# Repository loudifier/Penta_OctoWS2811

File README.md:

# Penta_OctoWS2811
Adapter board for driving 40 channels of WS2811-style addressable LED strips with a Teensy 4.1 microcontroller

This is a work in progress. A prototype board has been assembled, but I am waiting on parts to test Ethernet, and I am working on a sketch for testing that works better than the teensyduino examples for thousands of LEDs. Committing what I have so far.

[photo of board and LEDs]

The **Penta**_OctoWS2811 is effectively five of the [PJRC OctoWS2811 adapter](https://www.pjrc.com/store/octo28_adaptor.html) squished into a single board for an easy way to take full advantage of the Teensy 4.1's ability to use any set of GPIO pins with the OctoWS2811 library. Penta_OctoWS2811 also adds an Ethernet connector for use with ArtNet or other networked light controller, and a voltage regulator so the board and Teensy can be powered from the LED power supply without USB.

[image of schematic]

## Features

The Penta_OctoWS2811 board has 10 RJ45 ports, for a total of 40 output channels driven from 5V buffers through 100Ω termination resistors. Teensy 4.0 can also be used with this board, supporting up to 24 output channels.

## Usage

The instructions and guidelines on the PJRC website and Teensyduino example scketches for using a Teensy and OctoWS2811 to drive addressible LED strips over CAT6 wires apply equally to the PJRC OctoWS2811 adapter and the Penta_OctoWS2811 board, except for a few key features noted below.

### Output Pins

Teensy 4.1 digital output pins are connected to the following RJ45 ports:  
 Port - GPIO pins  
  J2 - 1, 2, 3, 4  
  J3 - 5, 6, 7, 8  
  J4 - 25, 26, 27, 28  
  J5 - 29, 30, 31, 32  
  J6 - 23, 22, 21, 20  
  J7 - 17, 16, 15, 14  
  J8 - 40, 39, 38, 37  
  J9 - 36, 35, 34, 33  
  J10 - 13, 18, 19, 9  
  J11 - 11, 12, 41, 24

Teensy 4.0 is compatible with the board, and will be connected to J2, J3, J6, J7, J10, and J11. In order to get a full 24 channels of output with Teensy 4.0, GPIO 0 can be used instead of GPIO 41 and GPIO 12 can be used instead of GPIO 24 by shorting jumper pads on the bottom of the board.

A frame sync output is provided, if you somehow need even more output channels and need to maintain accurate timing between multiple boards. The connector can also be useful for connecting to a single 3.3V-compatible LED strip. If you need to use GPIO 12 for SPI communication, you can cut and jump the appropriate pads on the bottom of the board to use GPIO 0 instead.

### Power

Just like the PJRC OctoWS2811 adapter, the Penta_OctoWS2811 board can be powered from your LED power supply. The Penta_OctoWS2811 board adds a voltage regulator for compatibility with newer 12V LED strips. If you are using 5V LEDs, the voltage regulator should be bypassed using the jumper pads on top of the board.

**The Teensy VUSB jumper must be cut if you plan to power the board from the LED power supply.** If you cut the VUSB jumper you can add a single header pin connection fom the Teensy VUSB pad to a corresponding pad on the board, which will allow the Teensy and board to be powered from the LED power supply or USB via a diode.

### Ethernet

## Board Design, Pre-assembled Boards

## Testing

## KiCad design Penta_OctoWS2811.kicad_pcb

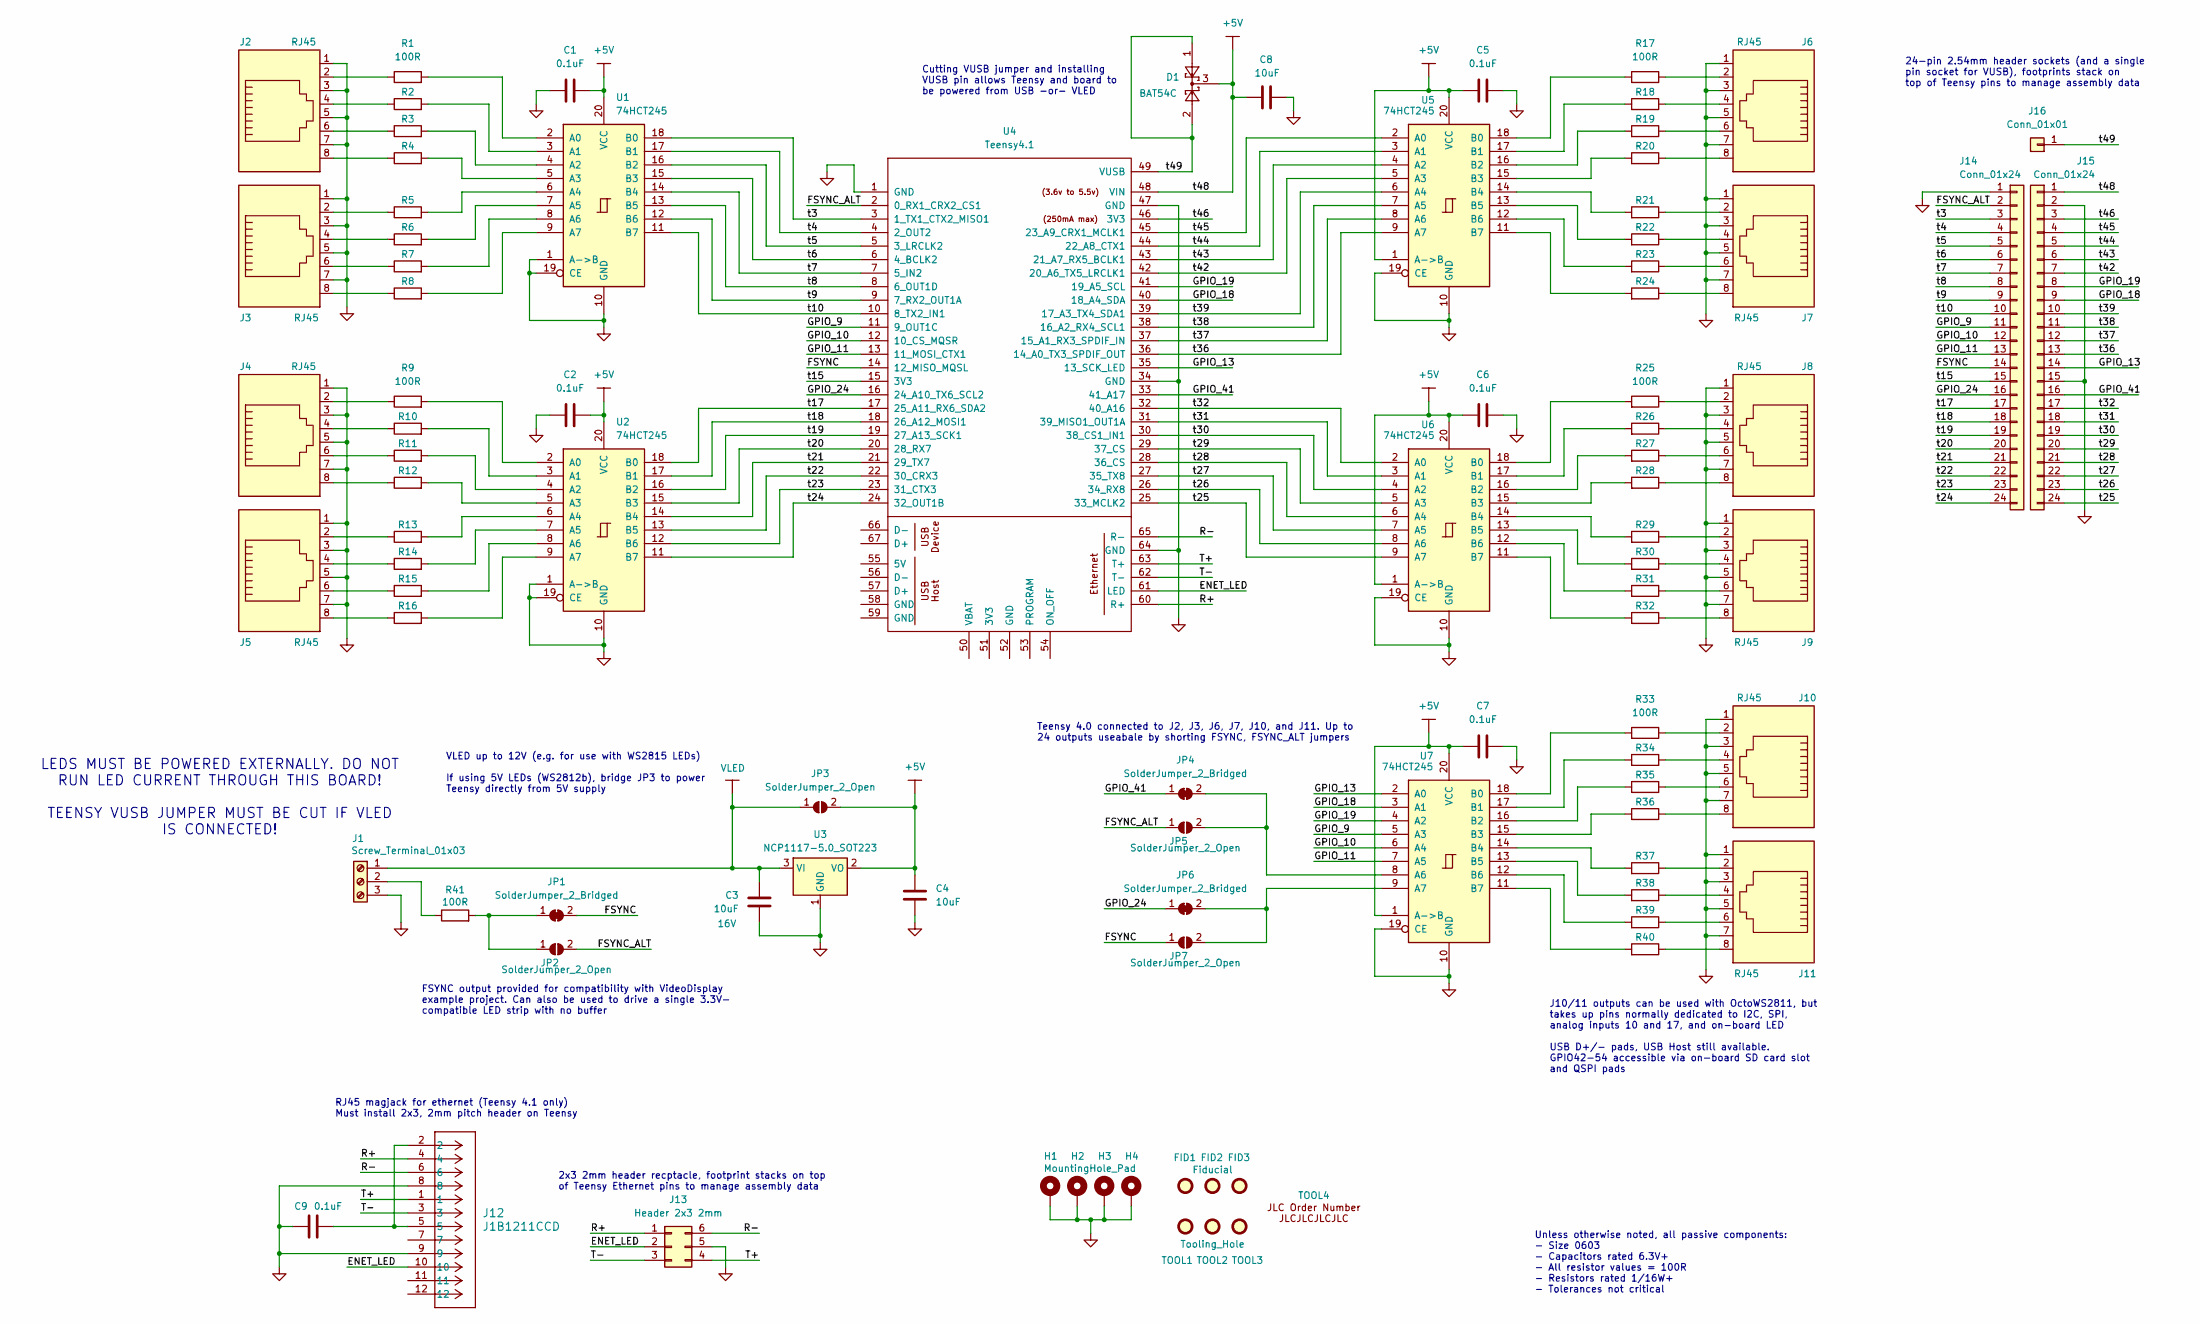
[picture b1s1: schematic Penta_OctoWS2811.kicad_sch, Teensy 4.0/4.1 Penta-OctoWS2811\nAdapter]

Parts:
C1, C2, C5, C6, C7, C9: 0.1uF; C_0603_1608Metric_Pad1.08x0.95mm_HandSolder; Manufacturer Part Number CC0603KRX7R9BB104
C3: 10uF; C_0603_1608Metric_Pad1.08x0.95mm_HandSolder; Voltage 16V; Manufacturer Part Number CL10A106MA8NRNC
C4, C8: 10uF; C_0603_1608Metric_Pad1.08x0.95mm_HandSolder; Manufacturer Part Number CL10A106MA8NRNC
D1: BAT54C; SOT-23; Manufacturer Part Number BAT54C,215
FID1, FID2, FID3: Fiducial; Fiducial_0.5mm_Mask1mm
H1, H2, H3, H4: MountingHole_Pad; MountingHole_5.3mm_M5_Pad
J1: Screw_Terminal_01x03; TerminalBlock_bornier-3_P5.08mm; Manufacturer Part Number DB127V-5.08-3P-GN-S
J2, J3, J4, J5, J6, J7, J8, J9, J10, J11: RJ45; HCTL HC-RJ45-5622-1-6; Manufacturer Part Number HC-RJ45-5622-1-6
J12: J1B1211CCD; CONN12_J1B1211CCD_WIZ; Manufacturer Part Number J1B1211CCD
J13: Header 2x3 2mm; PinSocket_2x03_P2.00mm_Vertical; Manufacturer Part Number ZX-PM2.0-2-3PY
J14, J15: Conn_01x24; PinSocket_1x24_P2.54mm_Vertical; Manufacturer Part Number X6511FV-24-C85D32
J16: Conn_01x01; PinSocket_1x01_P2.54mm_Vertical
JP1, JP4, JP6: SolderJumper_2_Bridged; SolderJumper-2_P1.3mm_Bridged_RoundedPad1.0x1.5mm
JP2, JP3, JP5, JP7: SolderJumper_2_Open; SolderJumper-2_P1.3mm_Open_RoundedPad1.0x1.5mm
R1, R2, R3, R4, R5, R6, R7, R8, R9, R10, R11, R12, R13, R14, R15, R16, R17, R18, R19, R20, R21, R22, R23, R24, R25, R26, R27, R28, R29, R30, R31, R32, R33, R34, R35, R36, R37, R38, R39, R40, R41: 100R; R_0603_1608Metric_Pad0.98x0.95mm_HandSolder; Manufacturer Part Number 0603WAF1000T5E
TOOL1, TOOL2, TOOL3: Tooling_Hole; Tooling Hole
TOOL4: Order Number
U1, U2, U5, U6, U7: 74HCT245; SOIC-20W_7.5x12.8mm_P1.27mm; Manufacturer Part Number 74HCT245D,653
U3: NCP1117-5.0_SOT223; SOT-223-3_TabPin2; Manufacturer Part Number NCP1117LPST50T3G
U4: Teensy4.1; Teensy41

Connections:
+5V: C1.2, C2.2, C4.2, C5.2, C6.2, C7.2, C8.2, D1.3, J15.1, JP3.2 (B), U1.20 (VCC), U2.20 (VCC), U3.2 (VO), U4.48 (VIN), U5.1 (A->B), U5.20 (VCC), U6.1 (A->B), U6.20 (VCC), U7.1 (A->B), U7.20 (VCC)
/ENET_LED: J12.10, J13.2, U4.61 (LED)
/FSYNC: J14.14, JP1.2 (B), JP7.1 (A), U4.14 (12_MISO_MQSL)
/FSYNC_ALT: J14.2, JP2.2 (B), JP5.1 (A), U4.2 (0_RX1_CRX2_CS1)
/GPIO_9: J14.11, U4.11 (9_OUT1C), U7.5 (A3)
/GPIO_10: J14.12, U4.12 (10_CS_MQSR), U7.6 (A4)
/GPIO_11: J14.13, U4.13 (11_MOSI_CTX1), U7.7 (A5)
/GPIO_13: J15.14, U4.35 (13_SCK_LED), U7.2 (A0)
/GPIO_18: J15.9, U4.40 (18_A4_SDA), U7.3 (A1)
/GPIO_19: J15.8, U4.41 (19_A5_SCL), U7.4 (A2)
/GPIO_24: J14.16, JP6.1 (A), U4.16 (24_A10_TX6_SCL2)
/GPIO_41: J15.16, JP4.1 (A), U4.33 (41_A17)
/R+: J12.4, J13.1, U4.60 (R+)
/R-: J12.6, J13.6, U4.65 (R-)
/T+: J12.1, J13.4, U4.63 (T+)
/T-: J12.3, J13.3, U4.62 (T-)
/t3: J14.3, U1.18 (B0), U4.3 (1_TX1_CTX2_MISO1)
/t4: J14.4, U1.17 (B1), U4.4 (2_OUT2)
/t5: J14.5, U1.16 (B2), U4.5 (3_LRCLK2)
/t6: J14.6, U1.15 (B3), U4.6 (4_BCLK2)
/t7: J14.7, U1.14 (B4), U4.7 (5_IN2)
/t8: J14.8, U1.13 (B5), U4.8 (6_OUT1D)
/t9: J14.9, U1.12 (B6), U4.9 (7_RX2_OUT1A)
/t10: J14.10, U1.11 (B7), U4.10 (8_TX2_IN1)
/t15: J14.15, U4.15 (3V3)
/t17: J14.17, U2.18 (B0), U4.17 (25_A11_RX6_SDA2)
/t18: J14.18, U2.17 (B1), U4.18 (26_A12_MOSI1)
/t19: J14.19, U2.16 (B2), U4.19 (27_A13_SCK1)
/t20: J14.20, U2.15 (B3), U4.20 (28_RX7)
/t21: J14.21, U2.14 (B4), U4.21 (29_TX7)
/t22: J14.22, U2.13 (B5), U4.22 (30_CRX3)
/t23: J14.23, U2.12 (B6), U4.23 (31_CTX3)
/t24: J14.24, U2.11 (B7), U4.24 (32_OUT1B)
/t25: J15.24, U4.25 (33_MCLK2), U6.9 (A7)
/t26: J15.23, U4.26 (34_RX8), U6.8 (A6)
/t27: J15.22, U4.27 (35_TX8), U6.7 (A5)
/t28: J15.21, U4.28 (36_CS), U6.6 (A4)
/t29: J15.20, U4.29 (37_CS), U6.5 (A3)
/t30: J15.19, U4.30 (38_CS1_IN1), U6.4 (A2)
/t31: J15.18, U4.31 (39_MISO1_OUT1A), U6.3 (A1)
/t32: J15.17, U4.32 (40_A16), U6.2 (A0)
/t36: J15.13, U4.36 (14_A0_TX3_SPDIF_OUT), U5.9 (A7)
/t37: J15.12, U4.37 (15_A1_RX3_SPDIF_IN), U5.8 (A6)
/t38: J15.11, U4.38 (16_A2_RX4_SCL1), U5.7 (A5)
/t39: J15.10, U4.39 (17_A3_TX4_SDA1), U5.6 (A4)
/t42: J15.7, U4.42 (20_A6_TX5_LRCLK1), U5.5 (A3)
/t43: J15.6, U4.43 (21_A7_RX5_BCLK1), U5.4 (A2)
/t44: J15.5, U4.44 (22_A8_CTX1), U5.3 (A1)
/t45: J15.4, U4.45 (23_A9_CRX1_MCLK1), U5.2 (A0)
/t46: J15.3, U4.46 (3V3)
/t49: D1.1, D1.2, J16.1, U4.49 (VUSB)
GND: C1.1, C2.1, C3.1, C4.1, C5.1, C6.1, C7.1, C8.1, C9.1, H1.1, H2.1, H3.1, H4.1, J1.3, J2.1, J2.3, J2.5, J2.7, J3.1, J3.3, J3.5, J3.7, J4.1, J4.3, J4.5, J4.7, J5.1, J5.3, J5.5, J5.7, J6.1, J6.3, J6.5, J6.7, J7.1, J7.3, J7.5, J7.7, J8.1, J8.3, J8.5, J8.7, J9.1, J9.3, J9.5, J9.7, J10.1, J10.3, J10.5, J10.7, J11.1, J11.3, J11.5, J11.7, J12.8, J12.9, J13.5, J14.1, J15.2, J15.15, U1.1 (A->B), U1.10 (GND), U1.19 (CE), U2.1 (A->B), U2.10 (GND), U2.19 (CE), U3.1 (GND), U4.1 (GND), U4.34 (GND), U4.47 (GND), U4.64 (GND), U5.10 (GND), U5.19 (CE), U6.10 (GND), U6.19 (CE), U7.10 (GND), U7.19 (CE)
unnamed: C9.2, J12.2, J12.5
unnamed: J1.2, R41.1
unnamed: J2.2, R1.1
unnamed: J2.4, R2.1
unnamed: J2.6, R3.1
unnamed: J2.8, R4.1
unnamed: J3.2, R5.1
unnamed: J3.4, R6.1
unnamed: J3.6, R7.1
unnamed: J3.8, R8.1
unnamed: J4.2, R9.1
unnamed: J4.4, R10.1
unnamed: J4.6, R11.1
unnamed: J4.8, R12.1
unnamed: J5.2, R13.1
unnamed: J5.4, R14.1
unnamed: J5.6, R15.1
unnamed: J5.8, R16.1
unnamed: J6.2, R17.1
unnamed: J6.4, R18.1
unnamed: J6.6, R19.1
unnamed: J6.8, R20.1
unnamed: J7.2, R21.1
unnamed: J7.4, R22.1
unnamed: J7.6, R23.1
unnamed: J7.8, R24.1
unnamed: J8.2, R25.1
unnamed: J8.4, R26.1
unnamed: J8.6, R27.1
unnamed: J8.8, R28.1
unnamed: J9.2, R29.1
unnamed: J9.4, R30.1
unnamed: J9.6, R31.1
unnamed: J9.8, R32.1
unnamed: J10.2, R33.1
unnamed: J10.4, R34.1
unnamed: J10.6, R35.1
unnamed: J10.8, R36.1
unnamed: J11.2, R37.1
unnamed: J11.4, R38.1
unnamed: J11.6, R39.1
unnamed: J11.8, R40.1
unnamed: JP1.1 (A), JP2.1 (A), R41.2
unnamed: JP4.2 (B), JP5.2 (B), U7.8 (A6)
unnamed: JP6.2 (B), JP7.2 (B), U7.9 (A7)
unnamed: R1.2, U1.2 (A0)
unnamed: R2.2, U1.3 (A1)
unnamed: R3.2, U1.4 (A2)
unnamed: R4.2, U1.5 (A3)
unnamed: R5.2, U1.6 (A4)
unnamed: R6.2, U1.7 (A5)
unnamed: R7.2, U1.8 (A6)
unnamed: R8.2, U1.9 (A7)
unnamed: R9.2, U2.2 (A0)
unnamed: R10.2, U2.3 (A1)
unnamed: R11.2, U2.4 (A2)
unnamed: R12.2, U2.5 (A3)
unnamed: R13.2, U2.6 (A4)
unnamed: R14.2, U2.7 (A5)
unnamed: R15.2, U2.8 (A6)
unnamed: R16.2, U2.9 (A7)
unnamed: R17.2, U5.18 (B0)
unnamed: R18.2, U5.17 (B1)
unnamed: R19.2, U5.16 (B2)
unnamed: R20.2, U5.15 (B3)
unnamed: R21.2, U5.14 (B4)
unnamed: R22.2, U5.13 (B5)
unnamed: R23.2, U5.12 (B6)
unnamed: R24.2, U5.11 (B7)
unnamed: R25.2, U6.18 (B0)
unnamed: R26.2, U6.17 (B1)
unnamed: R27.2, U6.16 (B2)
unnamed: R28.2, U6.15 (B3)
unnamed: R29.2, U6.14 (B4)
unnamed: R30.2, U6.13 (B5)
unnamed: R31.2, U6.12 (B6)
unnamed: R32.2, U6.11 (B7)
unnamed: R33.2, U7.18 (B0)
unnamed: R34.2, U7.17 (B1)
unnamed: R35.2, U7.16 (B2)
unnamed: R36.2, U7.15 (B3)
unnamed: R37.2, U7.14 (B4)
unnamed: R38.2, U7.13 (B5)
unnamed: R39.2, U7.12 (B6)
unnamed: R40.2, U7.11 (B7)
VLED: C3.2, J1.1, JP3.1 (A), U3.3 (VI)

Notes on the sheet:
Cutting VUSB jumper and installing VUSB pin allows Teensy and board to be powered from USB -or- VLED
2x3 2mm header recptacle, footprint stacks on top of Teensy Ethernet pins to manage assembly data
LEDS MUST BE POWERED EXTERNALLY. DO NOT RUN LED CURRENT THROUGH THIS BOARD! TEENSY VUSB JUMPER MUST BE CUT IF VLED IS CONNECTED!
24-pin 2.54mm header sockets (and a single pin socket for VUSB), footprints stack on top of Teensy pins to manage assembly data
Unless otherwise noted, all passive components: - Size 0603 - Capacitors rated 6.3V+ - All resistor values = 100R - Resistors rated 1/16W+ - Tolerances not critical
FSYNC output provided for compatibility with VideoDisplay example project. Can also be used to drive a single 3.3V- compatible LED strip with no buffer
J10/11 outputs can be used with OctoWS2811, but takes up pins normally dedicated to I2C, SPI, analog inputs 10 and 17, and on-board LED USB D+/- pads, USB Host still available. GPIO42-54 accessible via on-board SD card slot and QSPI pads
RJ45 magjack for ethernet (Teensy 4.1 only) Must install 2x3, 2mm pitch header on Teensy
Teensy 4.0 connected to J2, J3, J6, J7, J10, and J11. Up to 24 outputs useabale by shorting FSYNC, FSYNC_ALT jumpers
VLED up to 12V (e.g. for use with WS2815 LEDs) If using 5V LEDs (WS2812b), bridge JP3 to power Teensy directly from 5V supply

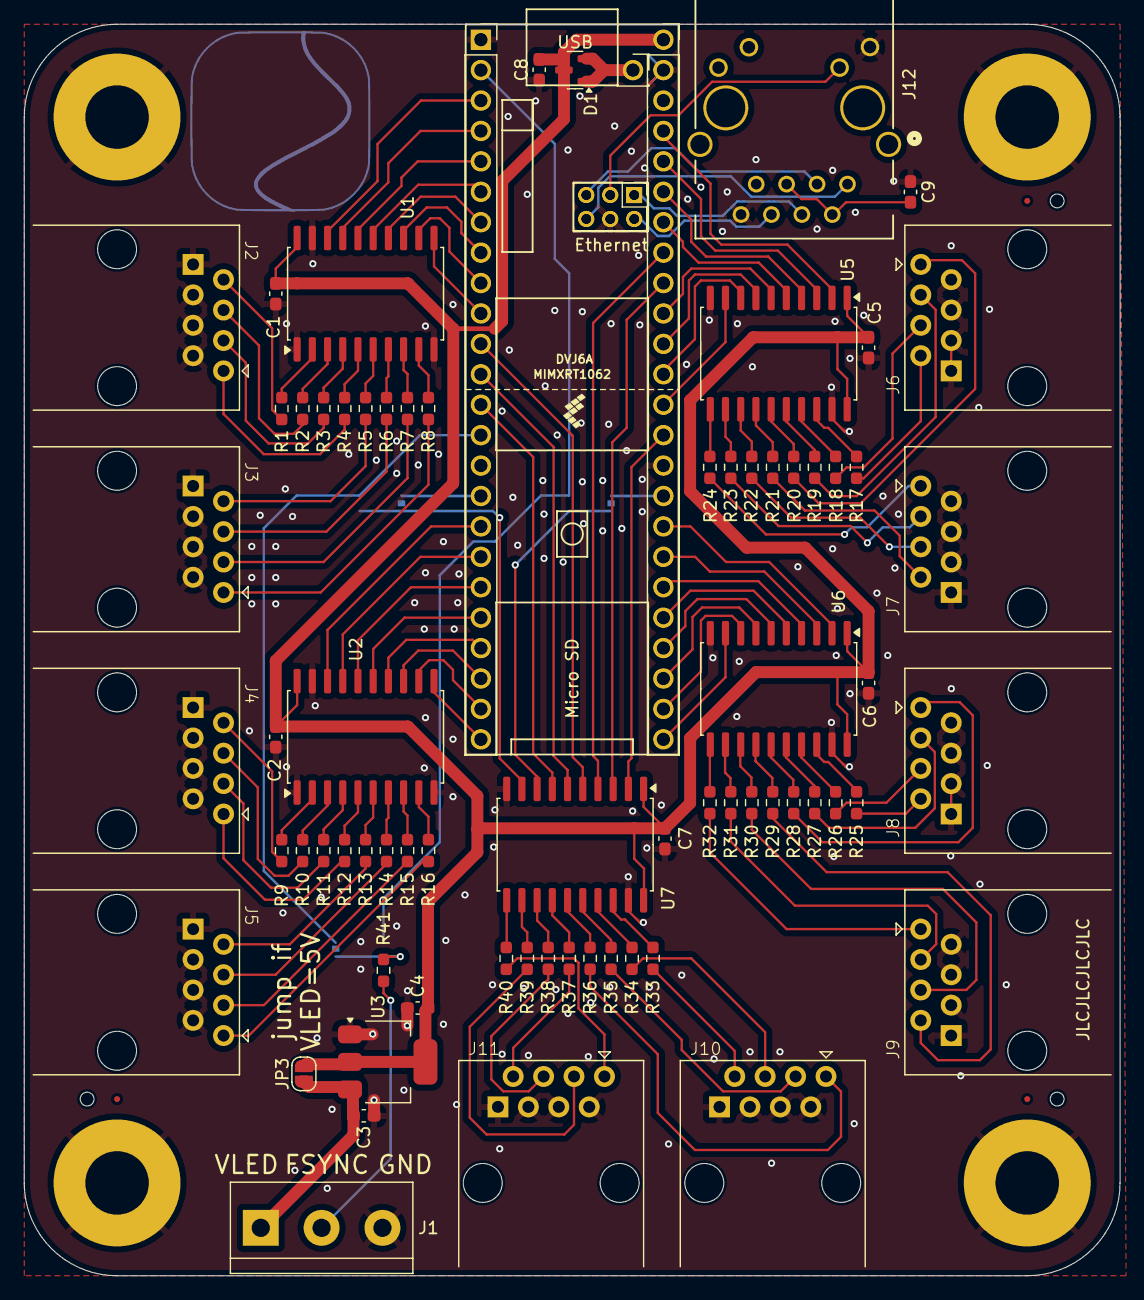
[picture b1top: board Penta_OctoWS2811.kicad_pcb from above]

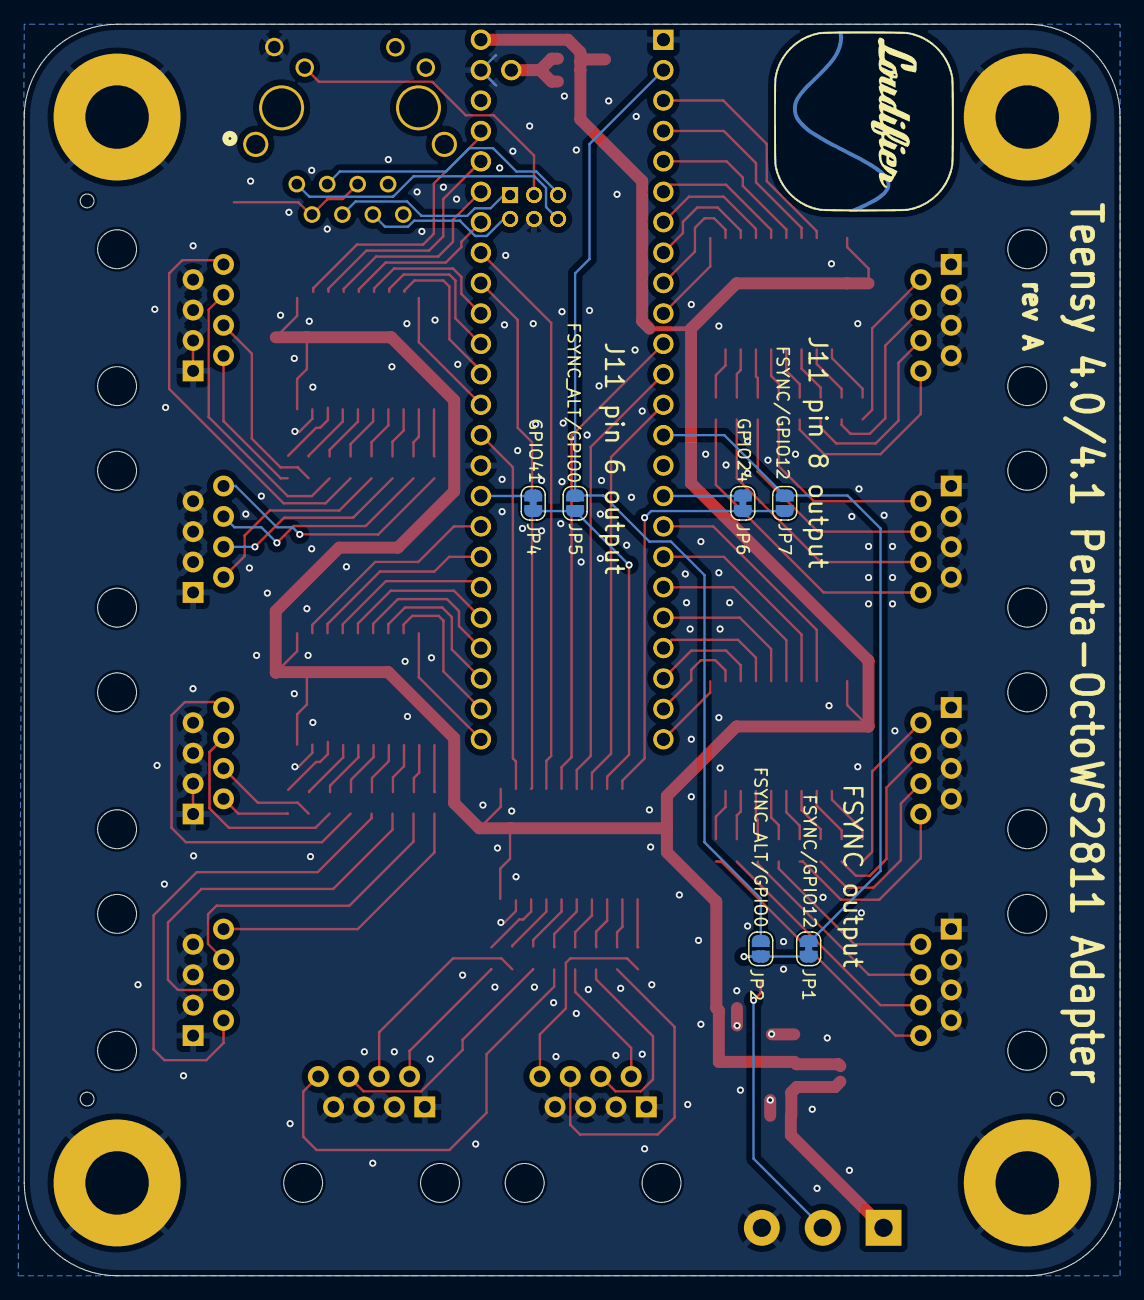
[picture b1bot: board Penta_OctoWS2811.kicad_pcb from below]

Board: 2 copper layers, 91.5 x 104.5 mm, 92 parts (6 on the bottom side), 138 nets.

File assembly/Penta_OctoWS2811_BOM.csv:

Designator,Qty,Description,Manufacturer Part Number,Manufacturer,Supplier,DNP
"C1,C2,C5,C6,C7,C9",6,CAP 0.1uF 0603 50V X7R 10%,CC0603KRX7R9BB104,Yageo,LCSC,
"C3,C4,C8",3,CAP 10uF 0603 25V X5R 20%,CL10A106MA8NRNC,Samsung,LCSC,
D1,1,"BAT54C dual Schottky barrier diode, common cathode","BAT54C,215",Nexperia,LCSC,
J1,1,"3 pin screw terminal block, 5.08mm pitch",DB127V-5.08-3P-GN-S,Dorabo,LCSC,
"J2,J3,J4,J5,J6,J7,J8,J9,J10,J11",10,"RJ45 jack, 8P8C, unshielded",HC-RJ45-5622-1-6,HCTL,LCSC,
J12,1,RJ45 magjack,J1B1211CCD ,WIZnet,LCSC,
J13,1,2x3 2mm header receptacle,ZX-PM2.0-2-3PY,Megastar,LCSC,
"J14,J15",2,1x24 2.54mm header receptacle,X6511FV-24-C85D32,Megastar,,
J16,1,Single pin 2.54mm header receptacle (use single segment from breakaway strip),,,,
"R1,R2,R3,R4,R5,R6,R7,R8,R9,R10,R11,R12,R13,R14,R15,R16,R17,R18,R19,R20,R21,R22,R23,R24,R25,R26,R27,R28,R29,R30,R31,R32,R33,R34,R35,R36,R37,R38,R39,R40,R41",41,RES 100R 0603 1/16W 1%,0603WAF1000T5E,Uniroyal,LCSC,
"U1,U2,U5,U6,U7",5,"74HCT245 Octal BUS Transceiver, 3-State outputs, TTL input","74HCT245D,653",Nexperia,LCSC,
U3,1,"NCP1117 1A Low drop-out regulator, Fixed 5.0V, SOT-223",NCP1117LPST50T3G,onsemi,LCSC,

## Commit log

2024-03-25 Fix VUSB diode. Diode from VIN to +5V was unnecessary, now using 2 parallel diodes from VUSB to VIN and tied VIN to +5V. Also fixed board name silkscreen typo.
